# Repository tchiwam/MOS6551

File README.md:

# MOS6551
PCB and software to replace a MXS6551X by a Atmega8535-AU

Enough legs to have fun and leave a header to add an Ethernet (SPI) or WIFI to ethernet.

Few ADC to push data from outside or play with some IO.

# Features
   -Flow control
   -Bigger FIFO

# Questions
   What is fast enough to emulate the 6551B 3MHZ
   Are all the critical pins in Hi-Z when booting.
   IRQ driven by the CS or pooled 

# Rationals
   Compromises:
    	328P lossing some flow controls or other signals
   	8535 Some ADC for playing with and bit bang the I2C or loose all ADC and keep the I2C
   Clock Speed: 
         14.7456, 11.0592, 7.3728, 3.6864 MHz best UART baud rate and least error.  Can somehow run without a crystal. The lowest possible clock for the least amount of power.

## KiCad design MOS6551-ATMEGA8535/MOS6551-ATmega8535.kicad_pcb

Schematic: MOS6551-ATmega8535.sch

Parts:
C1, C2: 22pF; C_0603_1608Metric
C3, C5, C7, C9: 1µF; C_1206_3216Metric
C4, C6, C8, C10: 1nF; C_1206_3216Metric
J1: Conn_02x03_Odd_Even; PinHeader_2x03_P2.54mm_Vertical_SMD
J2: Conn_02x02_Counter_Clockwise; PinHeader_2x02_P2.54mm_Vertical_SMD
J3, J4: Conn_01x14; PinHeader_1x14_P2.54mm_Vertical_SMD_Pin1Left
U1: ATmega88-20AU; TQFP-32_7x7mm_P0.8mm
U2: XC9572XL-VQ64; TQFP-64_10x10mm_P0.5mm
U3: MCP1700-3302E_SOT23; SOT-23
Y1: Crystal; Crystal_SMD_Qantek_QC5CB-2Pin_5x3.2mm

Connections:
+3V3: C7.1, C8.1, U2.3, U2.37, U3.2
+5V: C3.1, C4.1, C5.1, C6.1, C9.1, C10.1, J1.2, J4.14, U1.4, U1.6, U1.18, U2.26, U2.55, U3.3
CLK: J4.2, U2.34
CS0: J3.2, U2.40
DB0: J4.11, U2.43
DB1: J4.10, U2.44
DB2: J4.9, U2.45
DB3: J4.8, U2.46
DB4: J4.7, U2.47
DB5: J4.6, U2.48
DB6: J4.5, U2.49
DB7: J4.4, U2.50
GND: C1.1, C2.1, C3.2, C4.2, C5.2, C6.2, C7.2, C8.2, C9.2, C10.2, J1.6, J3.1, U1.3, U1.5, U1.21, U2.14, U2.21, U2.41, U2.54, U3.1
MISO: J1.1, U1.16
MOSI: J1.4, U1.15
unnamed: C1.2, U1.8, Y1.1
unnamed: C2.2, U1.7, Y1.2
unnamed: J2.1, U2.29
unnamed: J2.2, U2.30
unnamed: J2.3, U2.53
unnamed: J2.4, U2.28
unnamed: U1.12, U2.6
unnamed: U1.13, U2.7
unnamed: U1.17, U2.1
unnamed: U1.23, U2.58
unnamed: U1.24, U2.59
unnamed: U1.25, U2.60
unnamed: U1.26, U2.61
unnamed: U1.27, U2.62
unnamed: U1.28, U2.63
RS0: J3.13, U2.35
RS1: J3.14, U2.36
RxC: J3.5, U1.11
RxD: J3.12, U1.30
R~W: J4.1, U2.42
SCK: J1.3, U1.14
TxD: J3.10, U1.31
~CS1: J3.3, U2.39
~CTS: J3.9, U1.9
~DCD: J4.13, U1.1
~DSR: J4.12, U1.32
~DTR: J3.11, U1.2
~IRQ: J4.3, U2.38
~RESET: J1.5, J3.4, U1.29
~RTS: J3.8, U1.10

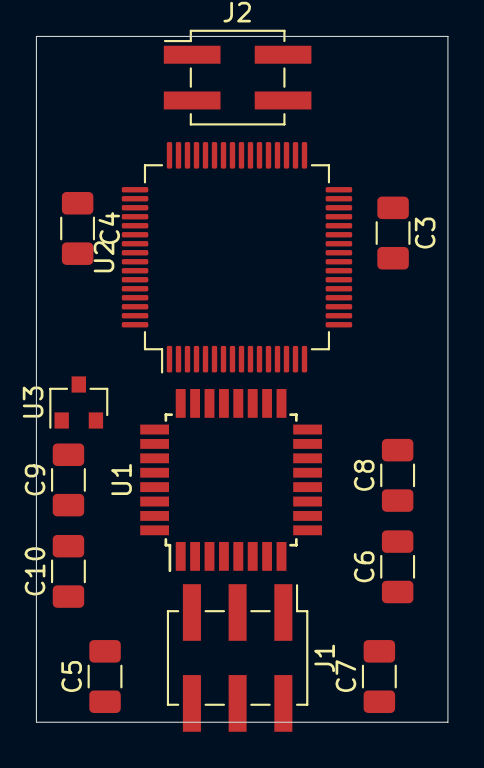
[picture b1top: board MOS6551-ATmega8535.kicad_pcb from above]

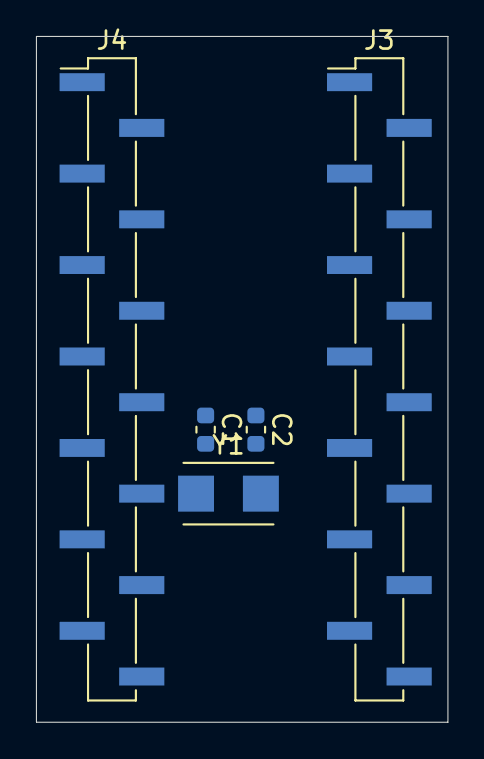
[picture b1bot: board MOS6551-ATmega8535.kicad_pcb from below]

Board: 2 copper layers, 22.9 x 38.1 mm, 18 parts (5 on the bottom side), 45 nets, no tracks yet.

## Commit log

2020-10-25 initial
2020-10-25 clean up
2020-11-08 Another darft
